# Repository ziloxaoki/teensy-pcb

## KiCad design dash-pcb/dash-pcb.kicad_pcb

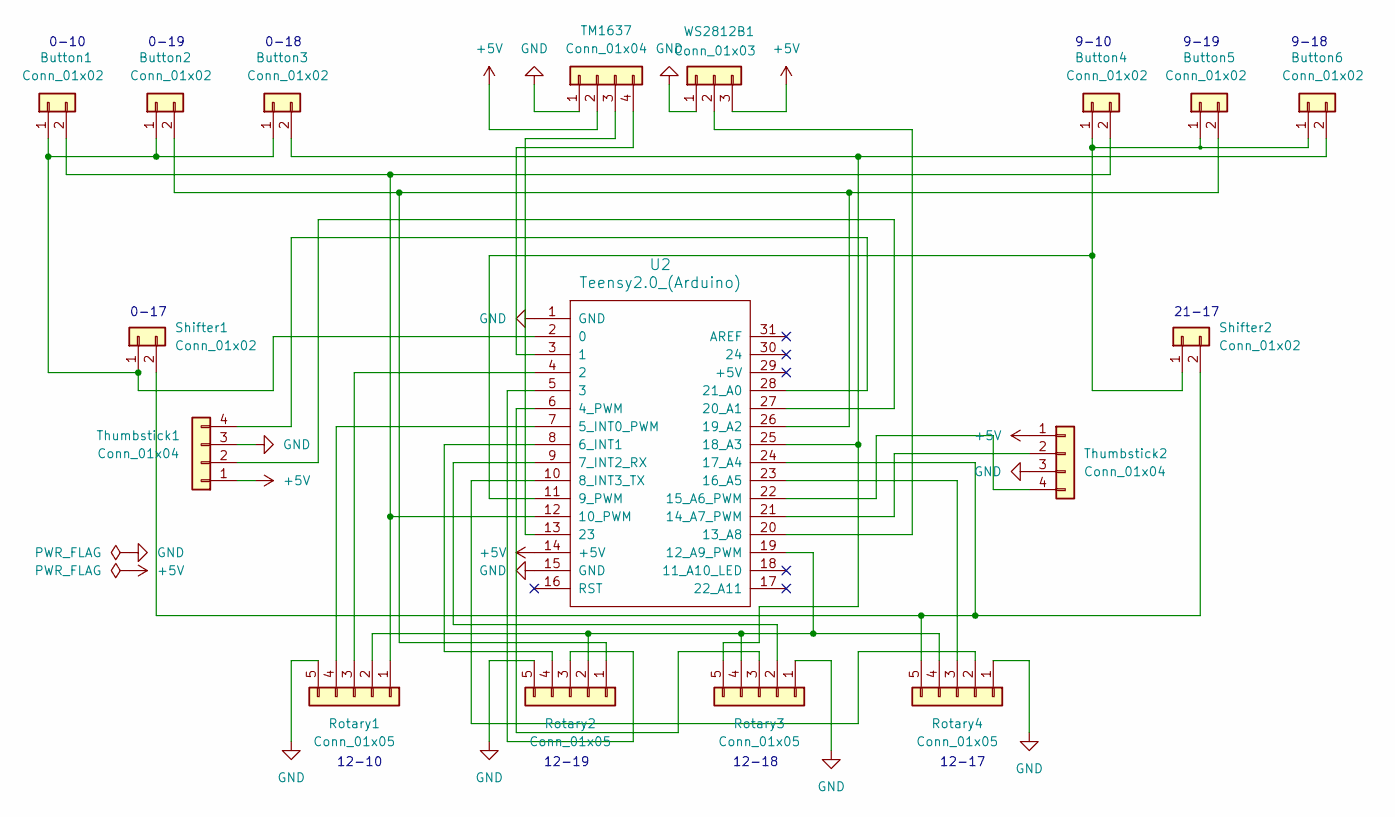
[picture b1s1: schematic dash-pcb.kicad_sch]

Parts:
Button1, Button2, Button3, Button4, Button5, Button6: Conn_01x02; JST_XH_B2B-XH-A_1x02_P2.50mm_Vertical
Rotary1, Rotary2, Rotary3, Rotary4: Conn_01x05; JST_XH_B5B-XH-A_1x05_P2.50mm_Vertical
Shifter1, Shifter2: Conn_01x02; JST_XH_B2B-XH-A_1x02_P2.50mm_Vertical
TM1637: Conn_01x04; JST_XH_B4B-XH-A_1x04_P2.50mm_Vertical
Thumbstick1, Thumbstick2: Conn_01x04; JST_XH_B4B-XH-A_1x04_P2.50mm_Vertical
U2: Teensy2.0_(Arduino); Teensy2.0
WS2812B1: Conn_01x03; JST_XH_B3B-XH-A_1x03_P2.50mm_Vertical

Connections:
+5V: TM1637.2, Thumbstick1.1, Thumbstick2.1, U2.14 (+5V), WS2812B1.3
GND: Rotary1.5, Rotary2.5, Rotary3.1, Rotary4.1, TM1637.1, Thumbstick1.3, Thumbstick2.3, U2.1 (GND), U2.15 (GND), WS2812B1.1
unnamed: Button1.1, Button2.1, Button3.1, Shifter1.1, U2.2 (0)
unnamed: Button1.2, Button4.2, Rotary1.1, U2.12 (10_PWM)
unnamed: Button2.2, Button5.2, Rotary2.1, U2.26 (19_A2)
unnamed: Button3.2, Button6.2, Rotary3.5, U2.25 (18_A3)
unnamed: Button4.1, Button5.1, Button6.1, Shifter2.1, U2.11 (9_PWM)
unnamed: Rotary1.2, Rotary2.2, Rotary3.4, Rotary4.4, U2.19 (12_A9_PWM)
unnamed: Rotary1.3, U2.4 (2)
unnamed: Rotary1.4, U2.7 (5_INT0_PWM)
unnamed: Rotary2.3, U2.5 (3)
unnamed: Rotary2.4, U2.8 (6_INT1)
unnamed: Rotary3.2, U2.9 (7_INT2_RX)
unnamed: Rotary3.3, U2.6 (4_PWM)
unnamed: Rotary4.2, U2.10 (8_INT3_TX)
unnamed: Rotary4.3, U2.23 (16_A5)
unnamed: Rotary4.5, Shifter1.2, Shifter2.2, U2.24 (17_A4)
unnamed: TM1637.3, U2.13 (23)
unnamed: TM1637.4, U2.3 (1)
unnamed: Thumbstick1.2, U2.27 (20_A1)
unnamed: Thumbstick1.4, U2.28 (21_A0)
unnamed: Thumbstick2.2, U2.21 (14_A7_PWM)
unnamed: Thumbstick2.4, U2.22 (15_A6_PWM)
unnamed: U2.20 (13_A8), WS2812B1.2

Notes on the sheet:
12-17
21-17
0-17
0-10
12-10
12-19
9-18
9-10
9-19
0-19
0-18
12-18

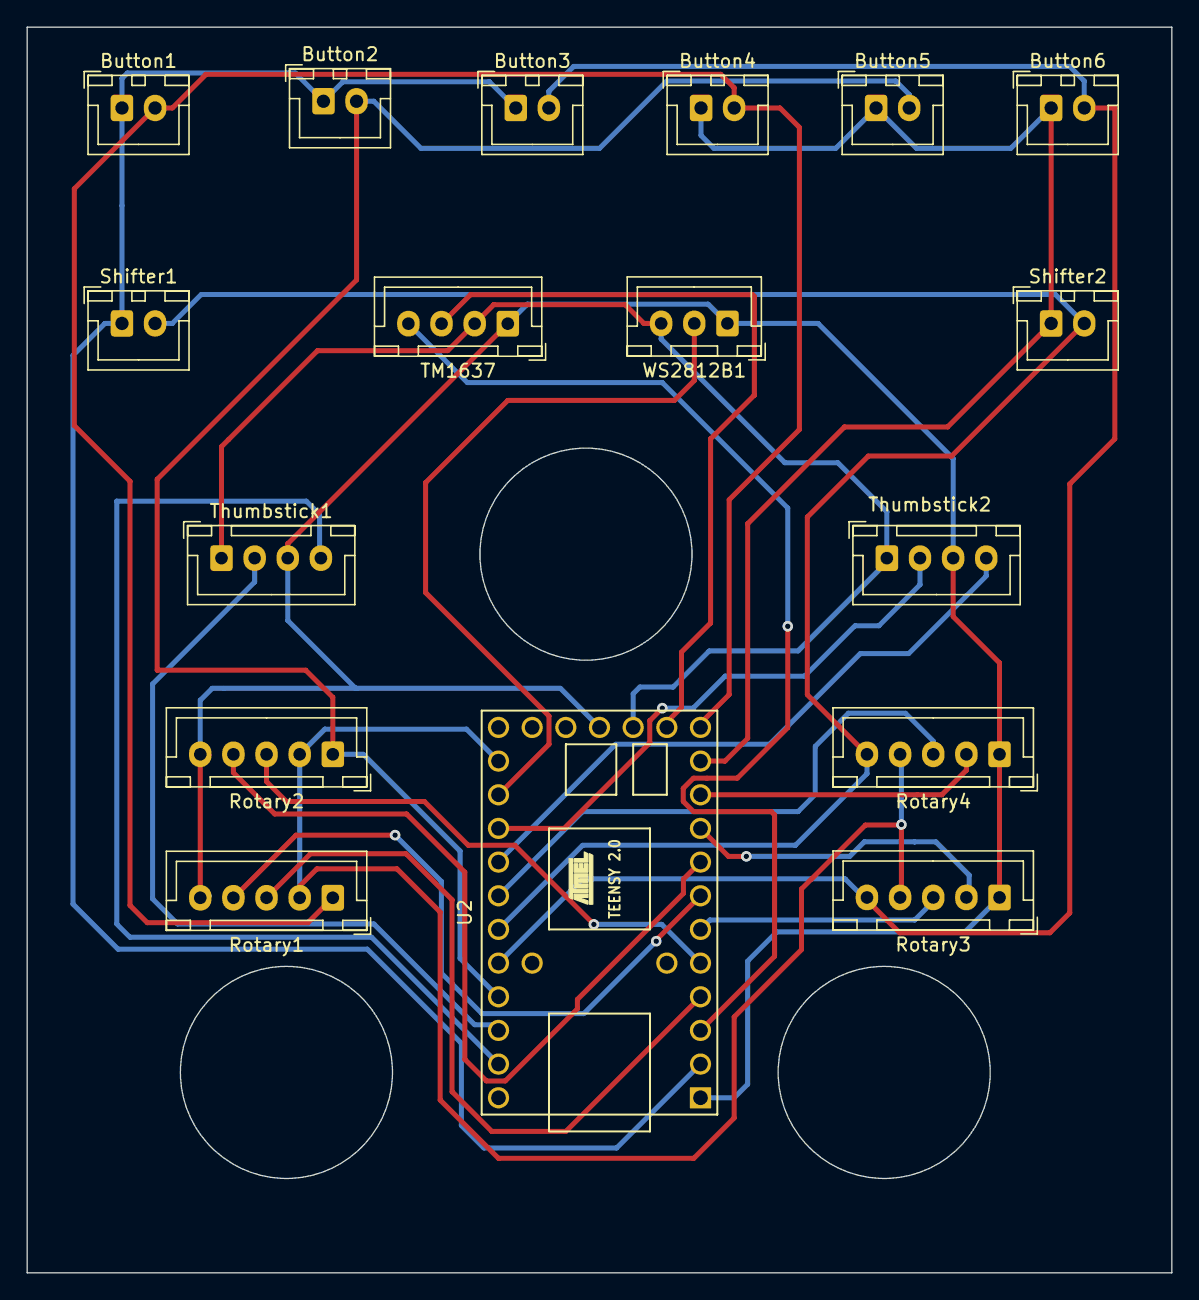
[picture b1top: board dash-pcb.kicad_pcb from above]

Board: 2 copper layers, 86.4 x 94.0 mm, 17 parts (0 on the bottom side), 24 nets.

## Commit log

2023-12-29 dash-pcb added
2024-01-27 fixed thumbstick 1 analogic pin
2024-02-03 improved tracks
